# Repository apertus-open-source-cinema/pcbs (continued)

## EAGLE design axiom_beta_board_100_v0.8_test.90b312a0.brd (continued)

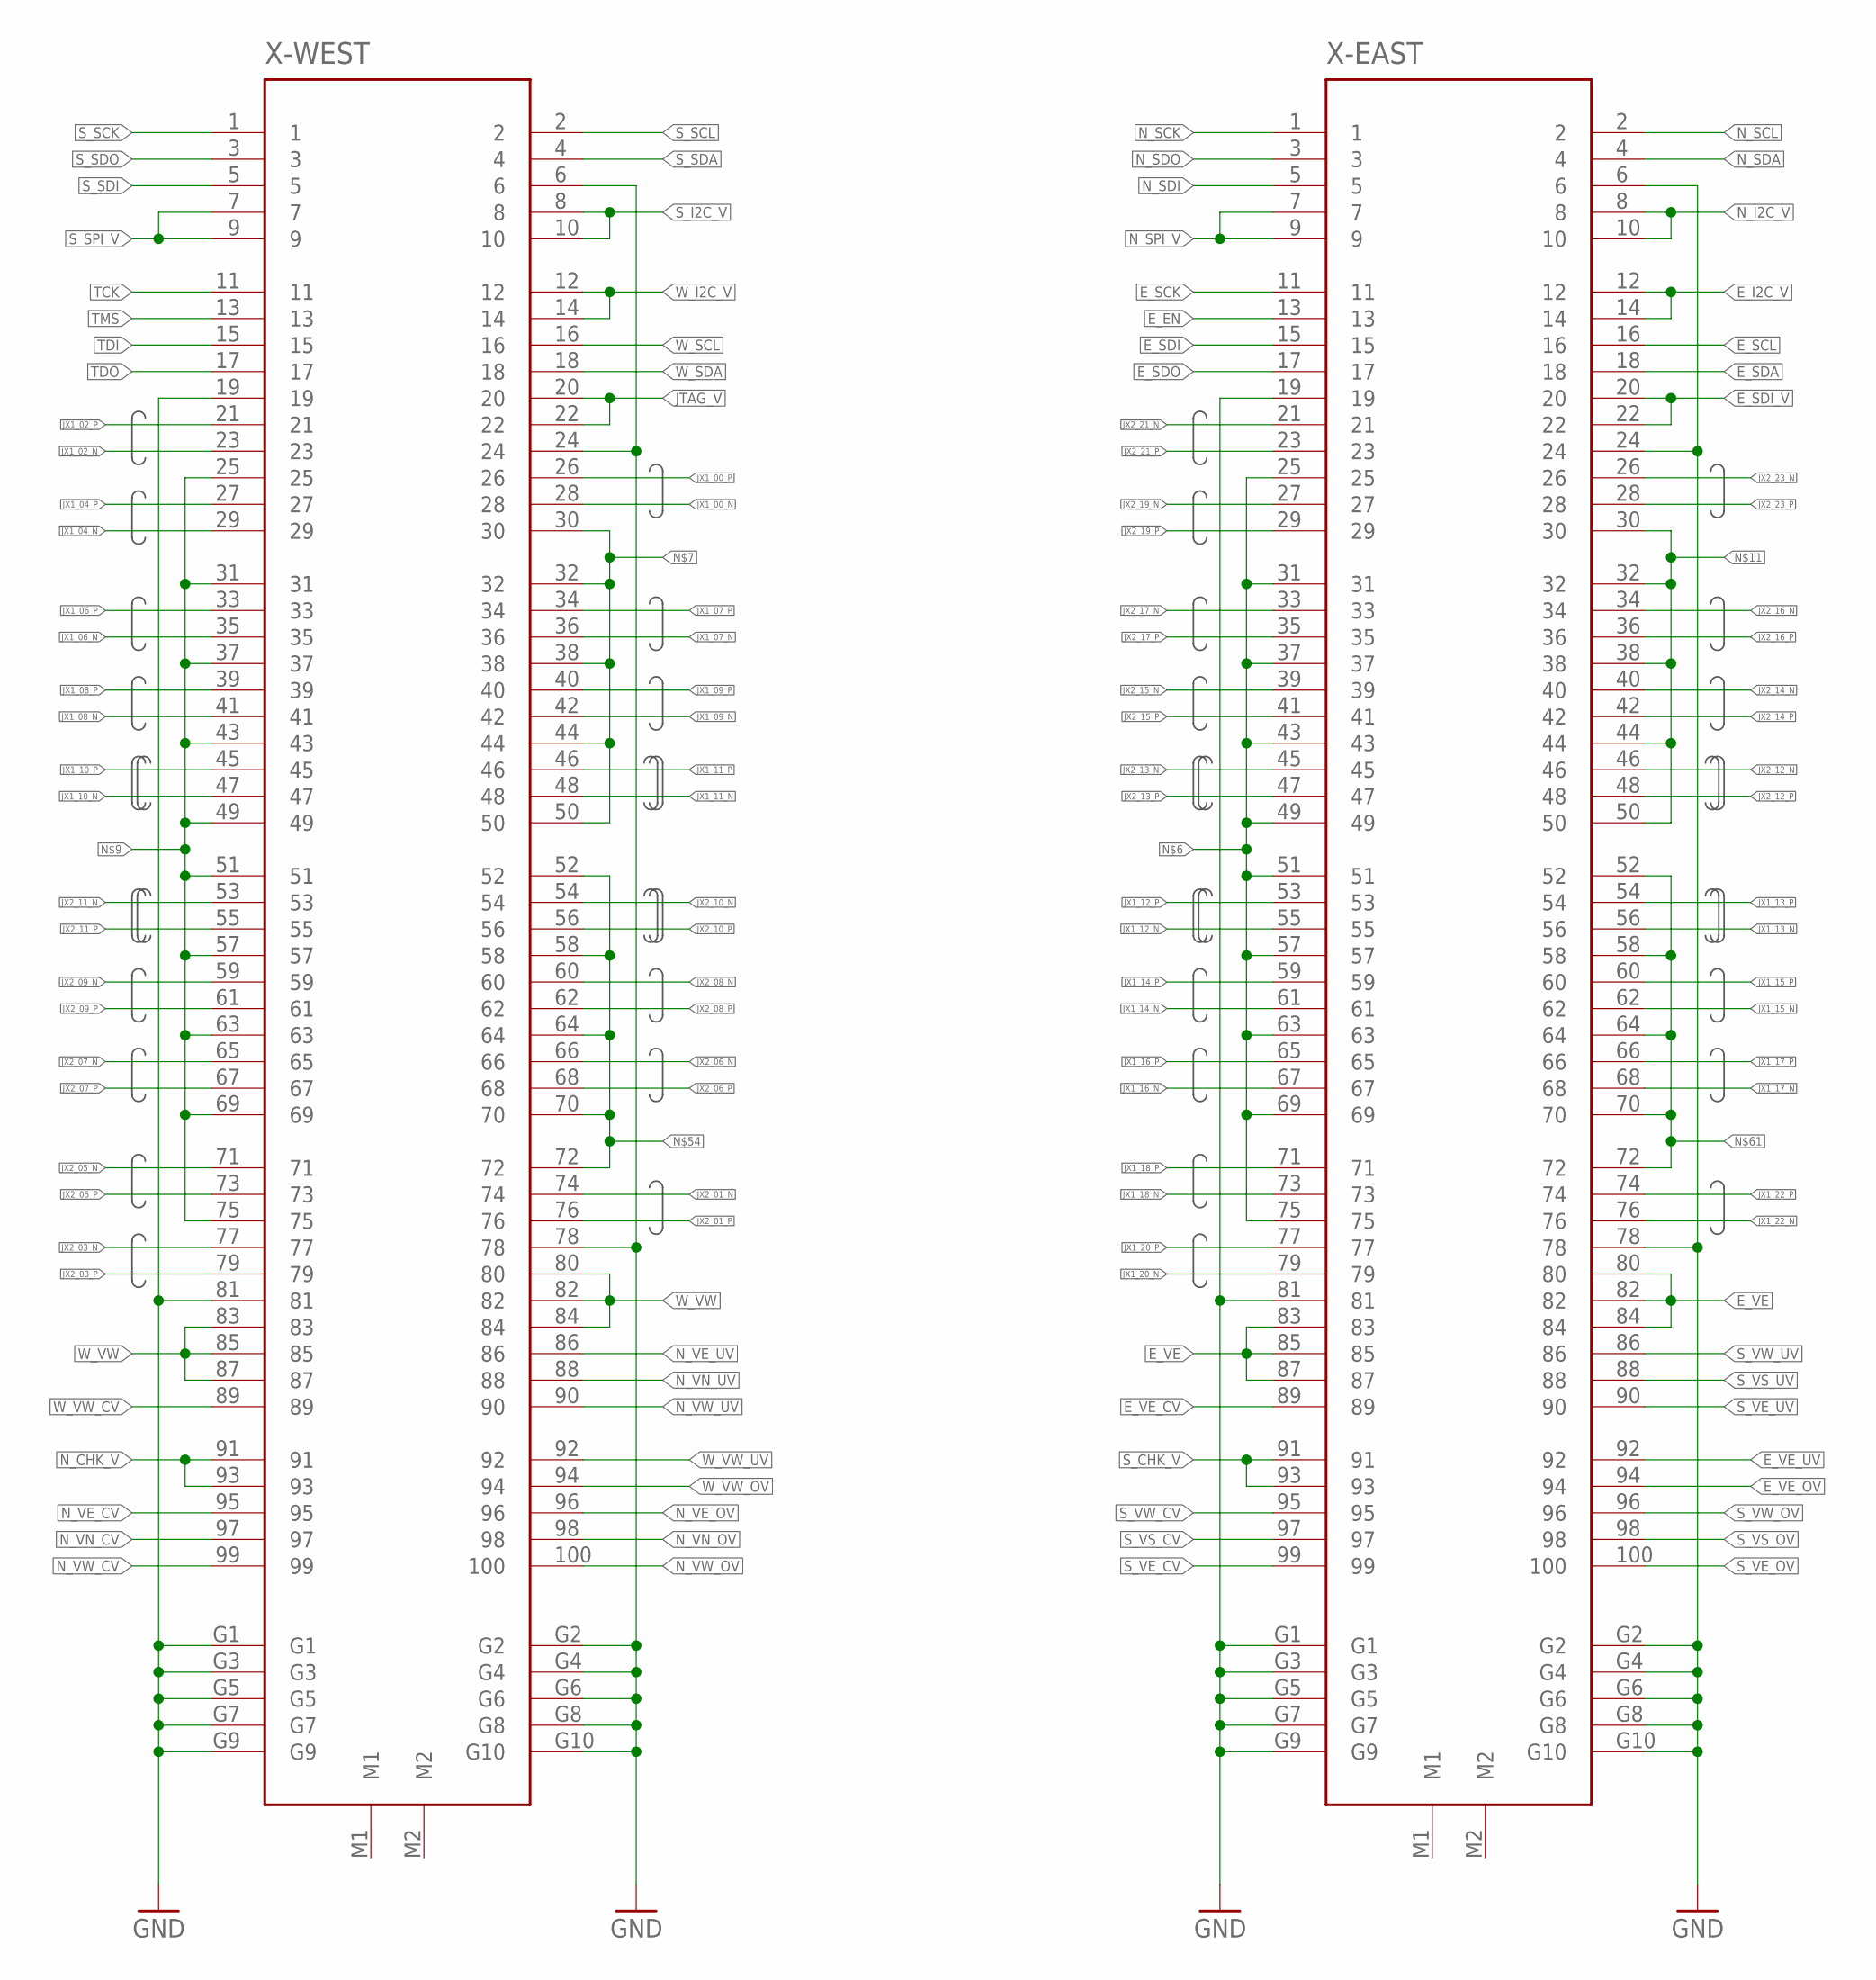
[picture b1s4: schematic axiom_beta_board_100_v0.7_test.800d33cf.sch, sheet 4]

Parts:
X-EAST: FX10-100/10S; FX10A-100S/10
X-WEST: FX10-100/10S; FX10A-100S/10

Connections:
E_EN: X-EAST.13; also elsewhere on the board
E_I2C_V: X-EAST.12, X-EAST.14; also elsewhere on the board
E_SCK: X-EAST.11; also elsewhere on the board
E_SCL: X-EAST.16; also elsewhere on the board
E_SDA: X-EAST.18; also elsewhere on the board
E_SDI: X-EAST.15; also elsewhere on the board
E_SDI_V: X-EAST.20, X-EAST.22; also elsewhere on the board
E_SDO: X-EAST.17; also elsewhere on the board
E_VE: X-EAST.80, X-EAST.82, X-EAST.83, X-EAST.84, X-EAST.85, X-EAST.87; also elsewhere on the board
E_VE_CV: X-EAST.89; also elsewhere on the board
E_VE_OV: X-EAST.94; also elsewhere on the board
E_VE_UV: X-EAST.92; also elsewhere on the board
JTAG_V: X-WEST.20, X-WEST.22; also elsewhere on the board
JX1_00_N: X-WEST.28; also elsewhere on the board
JX1_00_P: X-WEST.26; also elsewhere on the board
JX1_02_N: X-WEST.23; also elsewhere on the board
JX1_02_P: X-WEST.21; also elsewhere on the board
JX1_04_N: X-WEST.29; also elsewhere on the board
JX1_04_P: X-WEST.27; also elsewhere on the board
JX1_06_N: X-WEST.35; also elsewhere on the board
JX1_06_P: X-WEST.33; also elsewhere on the board
JX1_07_N: X-WEST.36; also elsewhere on the board
JX1_07_P: X-WEST.34; also elsewhere on the board
JX1_08_N: X-WEST.41; also elsewhere on the board
JX1_08_P: X-WEST.39; also elsewhere on the board
JX1_09_N: X-WEST.42; also elsewhere on the board
JX1_09_P: X-WEST.40; also elsewhere on the board
JX1_10_N: X-WEST.47; also elsewhere on the board
JX1_10_P: X-WEST.45; also elsewhere on the board
JX1_11_N: X-WEST.48; also elsewhere on the board
JX1_11_P: X-WEST.46; also elsewhere on the board
JX1_12_N: X-EAST.55; also elsewhere on the board
JX1_12_P: X-EAST.53; also elsewhere on the board
JX1_13_N: X-EAST.56; also elsewhere on the board
JX1_13_P: X-EAST.54; also elsewhere on the board
JX1_14_N: X-EAST.61; also elsewhere on the board
JX1_14_P: X-EAST.59; also elsewhere on the board
JX1_15_N: X-EAST.62; also elsewhere on the board
JX1_15_P: X-EAST.60; also elsewhere on the board
JX1_16_N: X-EAST.67; also elsewhere on the board
JX1_16_P: X-EAST.65; also elsewhere on the board
JX1_17_N: X-EAST.68; also elsewhere on the board
JX1_17_P: X-EAST.66; also elsewhere on the board
JX1_18_N: X-EAST.73; also elsewhere on the board
JX1_18_P: X-EAST.71; also elsewhere on the board
JX1_20_N: X-EAST.79; also elsewhere on the board
JX1_20_P: X-EAST.77; also elsewhere on the board
JX1_22_N: X-EAST.76; also elsewhere on the board
JX1_22_P: X-EAST.74; also elsewhere on the board
JX2_01_N: X-WEST.74; also elsewhere on the board
JX2_01_P: X-WEST.76; also elsewhere on the board
JX2_03_N: X-WEST.77; also elsewhere on the board
JX2_03_P: X-WEST.79; also elsewhere on the board
JX2_05_N: X-WEST.71; also elsewhere on the board
JX2_05_P: X-WEST.73; also elsewhere on the board
JX2_06_N: X-WEST.66; also elsewhere on the board
JX2_06_P: X-WEST.68; also elsewhere on the board
JX2_07_N: X-WEST.65; also elsewhere on the board
JX2_07_P: X-WEST.67; also elsewhere on the board
JX2_08_N: X-WEST.60; also elsewhere on the board
JX2_08_P: X-WEST.62; also elsewhere on the board
JX2_09_N: X-WEST.59; also elsewhere on the board
JX2_09_P: X-WEST.61; also elsewhere on the board
JX2_10_N: X-WEST.54; also elsewhere on the board
JX2_10_P: X-WEST.56; also elsewhere on the board
JX2_11_N: X-WEST.53; also elsewhere on the board
JX2_11_P: X-WEST.55; also elsewhere on the board
JX2_12_N: X-EAST.46; also elsewhere on the board
JX2_12_P: X-EAST.48; also elsewhere on the board
JX2_13_N: X-EAST.45; also elsewhere on the board
JX2_13_P: X-EAST.47; also elsewhere on the board
JX2_14_N: X-EAST.40; also elsewhere on the board
JX2_14_P: X-EAST.42; also elsewhere on the board
JX2_15_N: X-EAST.39; also elsewhere on the board
JX2_15_P: X-EAST.41; also elsewhere on the board
JX2_16_N: X-EAST.34; also elsewhere on the board
JX2_16_P: X-EAST.36; also elsewhere on the board
JX2_17_N: X-EAST.33; also elsewhere on the board
JX2_17_P: X-EAST.35; also elsewhere on the board
JX2_19_N: X-EAST.27; also elsewhere on the board
JX2_19_P: X-EAST.29; also elsewhere on the board
JX2_21_N: X-EAST.21; also elsewhere on the board
JX2_21_P: X-EAST.23; also elsewhere on the board
JX2_23_N: X-EAST.26; also elsewhere on the board
JX2_23_P: X-EAST.28; also elsewhere on the board
N_CHK_V: X-WEST.91, X-WEST.93; also elsewhere on the board
N_I2C_V: X-EAST.8, X-EAST.10; also elsewhere on the board
N_SCK: X-EAST.1; also elsewhere on the board
N_SCL: X-EAST.2; also elsewhere on the board
N_SDA: X-EAST.4; also elsewhere on the board
N_SDI: X-EAST.5; also elsewhere on the board
N_SDO: X-EAST.3; also elsewhere on the board
N_SPI_V: X-EAST.7, X-EAST.9; also elsewhere on the board
N_VE_CV: X-WEST.95; also elsewhere on the board
N_VE_OV: X-WEST.96; also elsewhere on the board
N_VE_UV: X-WEST.86; also elsewhere on the board
N_VN_CV: X-WEST.97; also elsewhere on the board
N_VN_OV: X-WEST.98; also elsewhere on the board
N_VN_UV: X-WEST.88; also elsewhere on the board
N_VW_CV: X-WEST.99; also elsewhere on the board
N_VW_OV: X-WEST.100; also elsewhere on the board
N_VW_UV: X-WEST.90; also elsewhere on the board
S_CHK_V: X-EAST.91, X-EAST.93; also elsewhere on the board
S_I2C_V: X-WEST.8, X-WEST.10; also elsewhere on the board
S_SCK: X-WEST.1; also elsewhere on the board
S_SCL: X-WEST.2; also elsewhere on the board
S_SDA: X-WEST.4; also elsewhere on the board
S_SDI: X-WEST.5; also elsewhere on the board
S_SDO: X-WEST.3; also elsewhere on the board
S_SPI_V: X-WEST.7, X-WEST.9; also elsewhere on the board
S_VE_CV: X-EAST.99; also elsewhere on the board
S_VE_OV: X-EAST.100; also elsewhere on the board
S_VE_UV: X-EAST.90; also elsewhere on the board
S_VS_CV: X-EAST.97; also elsewhere on the board
S_VS_OV: X-EAST.98; also elsewhere on the board
S_VS_UV: X-EAST.88; also elsewhere on the board
S_VW_CV: X-EAST.95; also elsewhere on the board
S_VW_OV: X-EAST.96; also elsewhere on the board
S_VW_UV: X-EAST.86; also elsewhere on the board
TCK: X-WEST.11; also elsewhere on the board
TDI: X-WEST.15; also elsewhere on the board
TDO: X-WEST.17; also elsewhere on the board
TMS: X-WEST.13; also elsewhere on the board
W_I2C_V: X-WEST.12, X-WEST.14; also elsewhere on the board
W_SCL: X-WEST.16; also elsewhere on the board
W_SDA: X-WEST.18; also elsewhere on the board
W_VW: X-WEST.80, X-WEST.82, X-WEST.83, X-WEST.84, X-WEST.85, X-WEST.87; also elsewhere on the board
W_VW_CV: X-WEST.89; also elsewhere on the board
W_VW_OV: X-WEST.94; also elsewhere on the board
W_VW_UV: X-WEST.92; also elsewhere on the board

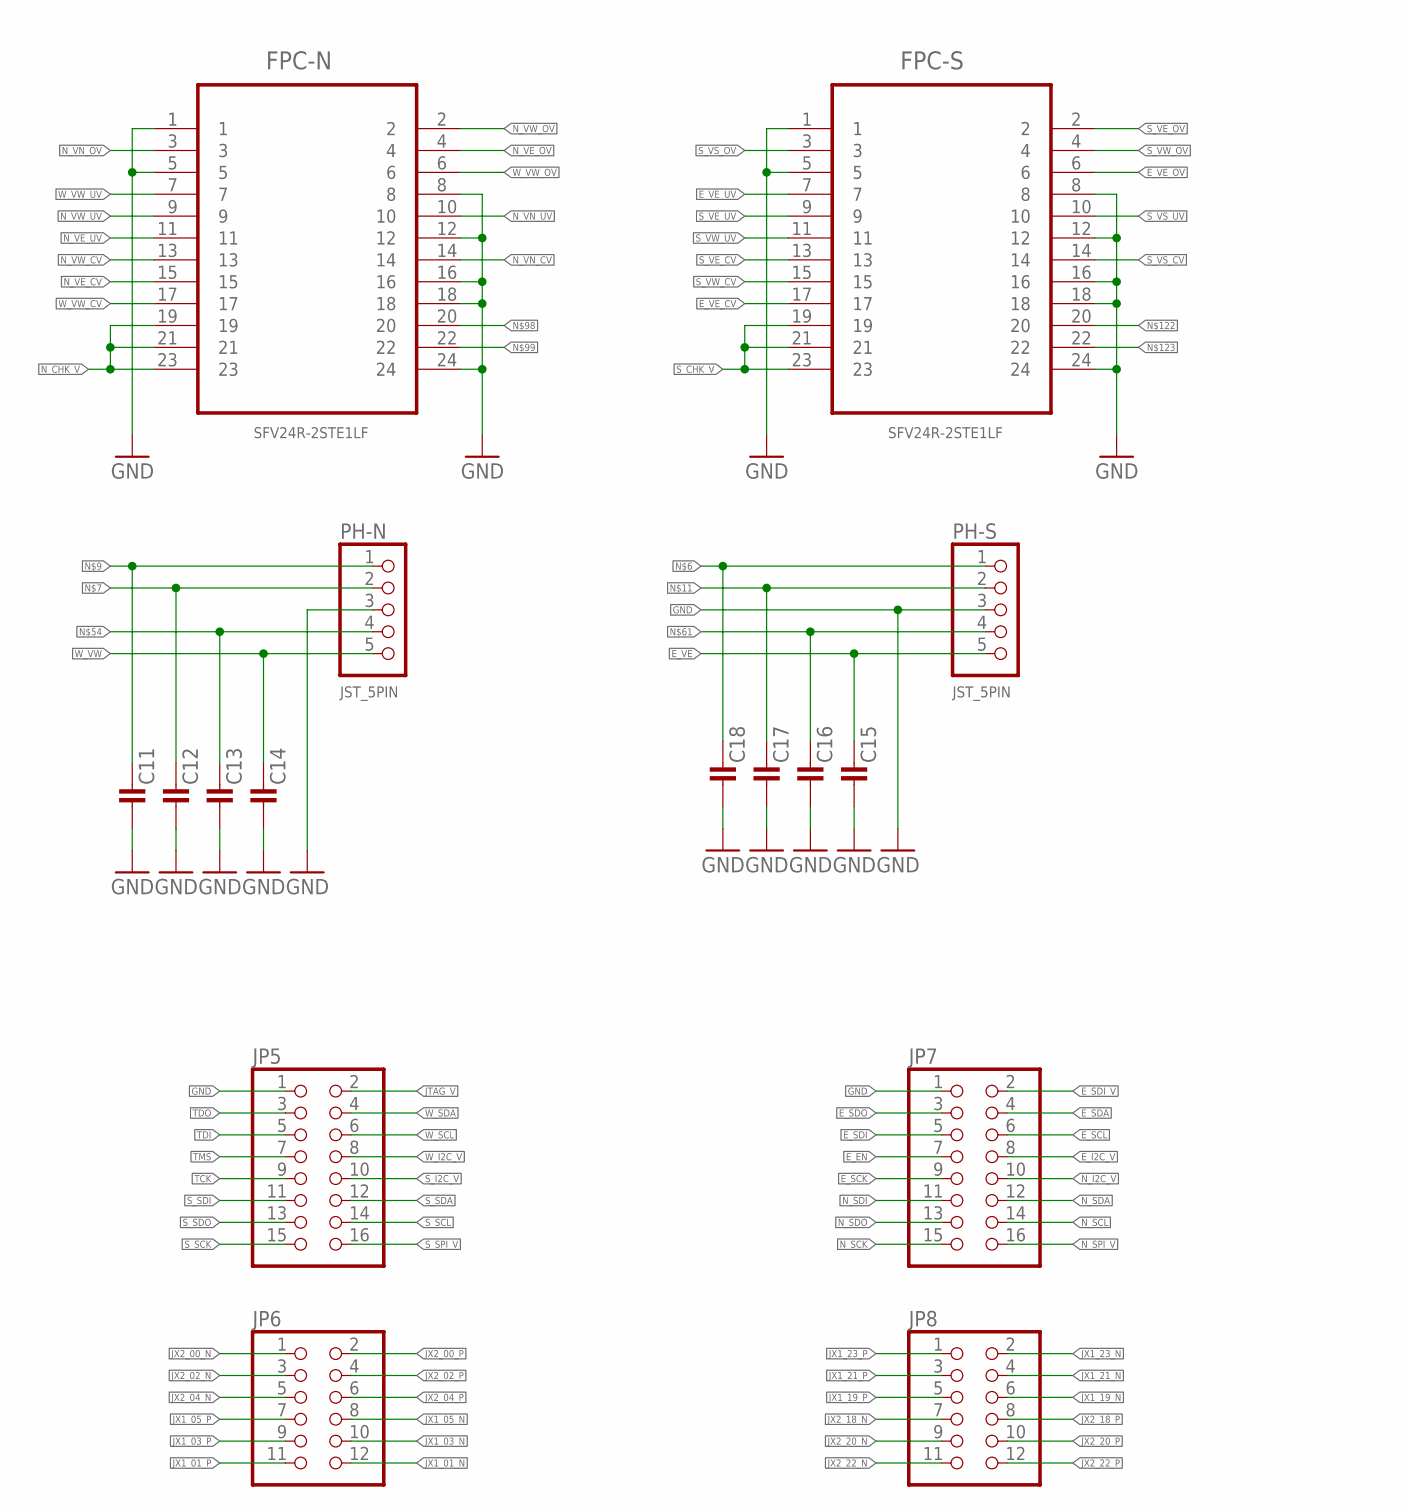
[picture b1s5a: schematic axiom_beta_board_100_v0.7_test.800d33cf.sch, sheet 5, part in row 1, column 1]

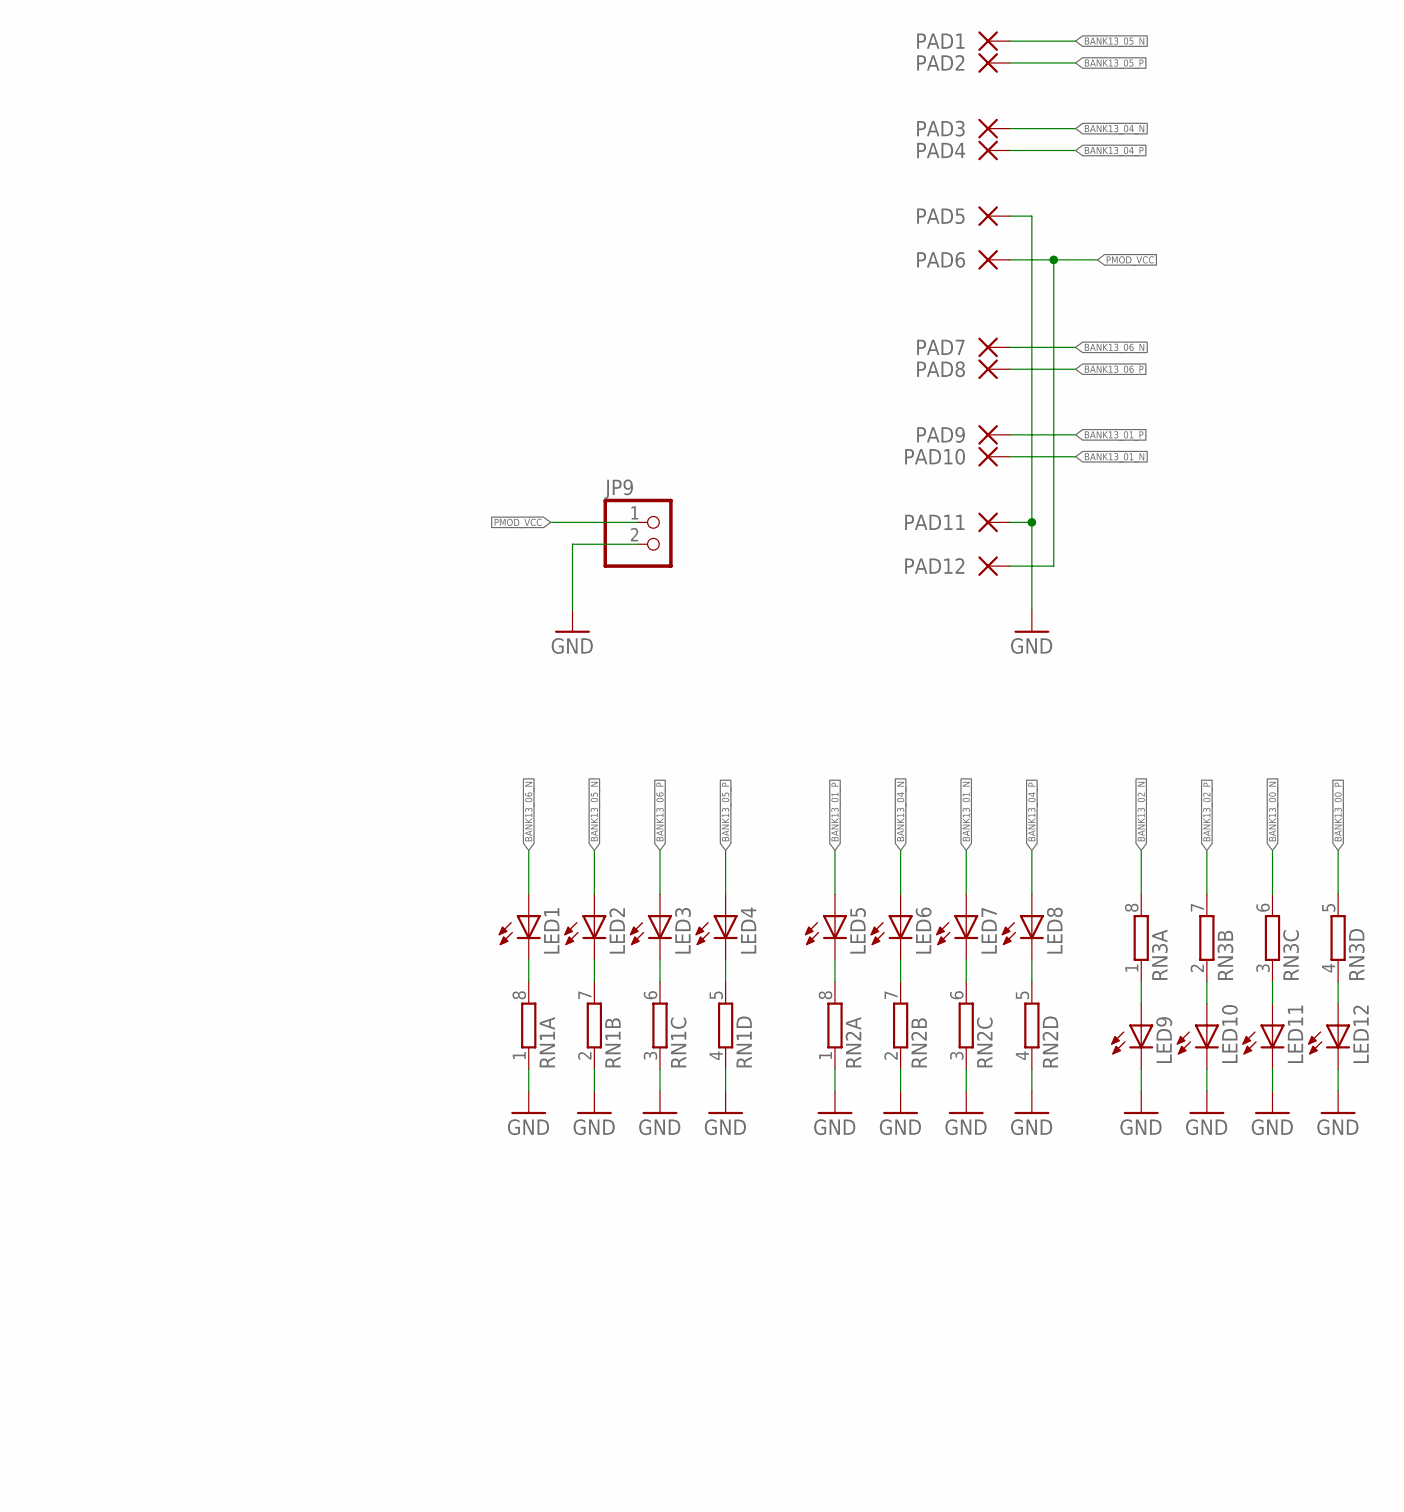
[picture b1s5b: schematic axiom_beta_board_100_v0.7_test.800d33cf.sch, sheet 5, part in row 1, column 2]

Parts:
C11, C12, C13, C14, C15, C16, C17, C18: C1206-B; 1206-B
FPC-N: SFV24R-2STE1LF; FCI_SFV24R-2STE1LF
FPC-S: SFV24R-2STE1LF; FCI_SFV24R-2STE1LF
JP5, JP7: PINHD-2X08_2.54; 2X08
JP6, JP8: PINHD-2X06_2.54; 2X06
JP9: PINHD-1X02_2.54; 1X02
LED1, LED2, LED3, LED4, LED5, LED6, LED7, LED8, LED9, LED10, LED11, LED12: LEDCHIPLED_0603; CHIPLED_0603
PAD1, PAD2, PAD3, PAD4, PAD5, PAD6, PAD7, PAD8, PAD9, PAD10, PAD11, PAD12: SMD-PAD1.6X3.8MM-U; 1.6X3.8U-MM
PH-N: JST_5PIN; JST-PH-5-SMT-RA
PH-S: JST_5PIN; JST-PH-5-SMT-RA
RN1, RN2, RN3: 4R-NCAY16; CAY16

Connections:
BANK13_00_N: RN3.6 (2); also elsewhere on the board
BANK13_00_P: RN3.5 (2); also elsewhere on the board
BANK13_01_N: LED7.A, PAD10.1; also elsewhere on the board
BANK13_01_P: LED5.A, PAD9.1; also elsewhere on the board
BANK13_02_N: RN3.8 (2); also elsewhere on the board
BANK13_02_P: RN3.7 (2); also elsewhere on the board
BANK13_04_N: LED6.A, PAD3.1; also elsewhere on the board
BANK13_04_P: LED8.A, PAD4.1; also elsewhere on the board
BANK13_05_N: LED2.A, PAD1.1; also elsewhere on the board
BANK13_05_P: LED4.A, PAD2.1; also elsewhere on the board
BANK13_06_N: LED1.A, PAD7.1; also elsewhere on the board
BANK13_06_P: LED3.A, PAD8.1; also elsewhere on the board
E_EN: JP7.7; also elsewhere on the board
E_I2C_V: JP7.8; also elsewhere on the board
E_SCK: JP7.9; also elsewhere on the board
E_SCL: JP7.6; also elsewhere on the board
E_SDA: JP7.4; also elsewhere on the board
E_SDI: JP7.5; also elsewhere on the board
E_SDI_V: JP7.2; also elsewhere on the board
E_SDO: JP7.3; also elsewhere on the board
E_VE: C15.1, PH-S.5; also elsewhere on the board
E_VE_CV: FPC-S.17; also elsewhere on the board
E_VE_OV: FPC-S.6; also elsewhere on the board
E_VE_UV: FPC-S.7; also elsewhere on the board
JTAG_V: JP5.2; also elsewhere on the board
JX1_01_N: JP6.12; also elsewhere on the board
JX1_01_P: JP6.11; also elsewhere on the board
JX1_03_N: JP6.10; also elsewhere on the board
JX1_03_P: JP6.9; also elsewhere on the board
JX1_05_N: JP6.8; also elsewhere on the board
JX1_05_P: JP6.7; also elsewhere on the board
JX1_19_N: JP8.6; also elsewhere on the board
JX1_19_P: JP8.5; also elsewhere on the board
JX1_21_N: JP8.4; also elsewhere on the board
JX1_21_P: JP8.3; also elsewhere on the board
JX1_23_N: JP8.2; also elsewhere on the board
JX1_23_P: JP8.1; also elsewhere on the board
JX2_00_N: JP6.1; also elsewhere on the board
JX2_00_P: JP6.2; also elsewhere on the board
JX2_02_N: JP6.3; also elsewhere on the board
JX2_02_P: JP6.4; also elsewhere on the board
JX2_04_N: JP6.5; also elsewhere on the board
JX2_04_P: JP6.6; also elsewhere on the board
JX2_18_N: JP8.7; also elsewhere on the board
JX2_18_P: JP8.8; also elsewhere on the board
JX2_20_N: JP8.9; also elsewhere on the board
JX2_20_P: JP8.10; also elsewhere on the board
JX2_22_N: JP8.11; also elsewhere on the board
JX2_22_P: JP8.12; also elsewhere on the board
unnamed: LED1.C, RN1.8 (2)
unnamed: LED2.C, RN1.7 (2)
unnamed: LED3.C, RN1.6 (2)
unnamed: LED4.C, RN1.5 (2)
unnamed: LED5.C, RN2.8 (2)
unnamed: LED6.C, RN2.7 (2)
unnamed: LED7.C, RN2.6 (2)
unnamed: LED8.C, RN2.5 (2)
unnamed: LED9.A, RN3.1
unnamed: LED10.A, RN3.2 (1)
unnamed: LED11.A, RN3.3 (1)
unnamed: LED12.A, RN3.4 (1)
N_CHK_V: FPC-N.19, FPC-N.21, FPC-N.23; also elsewhere on the board
N_I2C_V: JP7.10; also elsewhere on the board
N_SCK: JP7.15; also elsewhere on the board
N_SCL: JP7.14; also elsewhere on the board
N_SDA: JP7.12; also elsewhere on the board
N_SDI: JP7.11; also elsewhere on the board
N_SDO: JP7.13; also elsewhere on the board
N_SPI_V: JP7.16; also elsewhere on the board
N_VE_CV: FPC-N.15; also elsewhere on the board
N_VE_OV: FPC-N.4; also elsewhere on the board
N_VE_UV: FPC-N.11; also elsewhere on the board
N_VN_CV: FPC-N.14; also elsewhere on the board
N_VN_OV: FPC-N.3; also elsewhere on the board
N_VN_UV: FPC-N.10; also elsewhere on the board
N_VW_CV: FPC-N.13; also elsewhere on the board
N_VW_OV: FPC-N.2; also elsewhere on the board
N_VW_UV: FPC-N.9; also elsewhere on the board
PMOD_VCC: JP9.1, PAD6.1, PAD12.1
S_CHK_V: FPC-S.19, FPC-S.21, FPC-S.23; also elsewhere on the board
S_I2C_V: JP5.10; also elsewhere on the board
S_SCK: JP5.15; also elsewhere on the board
S_SCL: JP5.14; also elsewhere on the board
S_SDA: JP5.12; also elsewhere on the board
S_SDI: JP5.11; also elsewhere on the board
S_SDO: JP5.13; also elsewhere on the board
S_SPI_V: JP5.16; also elsewhere on the board
S_VE_CV: FPC-S.13; also elsewhere on the board
S_VE_OV: FPC-S.2; also elsewhere on the board
S_VE_UV: FPC-S.9; also elsewhere on the board
S_VS_CV: FPC-S.14; also elsewhere on the board
S_VS_OV: FPC-S.3; also elsewhere on the board
S_VS_UV: FPC-S.10; also elsewhere on the board
S_VW_CV: FPC-S.15; also elsewhere on the board
S_VW_OV: FPC-S.4; also elsewhere on the board
S_VW_UV: FPC-S.11; also elsewhere on the board
TCK: JP5.9; also elsewhere on the board
TDI: JP5.5; also elsewhere on the board
TDO: JP5.3; also elsewhere on the board
TMS: JP5.7; also elsewhere on the board
W_I2C_V: JP5.8; also elsewhere on the board
W_SCL: JP5.6; also elsewhere on the board
W_SDA: JP5.4; also elsewhere on the board
W_VW: C14.1, PH-N.5; also elsewhere on the board
W_VW_CV: FPC-N.17; also elsewhere on the board
W_VW_OV: FPC-N.6; also elsewhere on the board
W_VW_UV: FPC-N.7; also elsewhere on the board

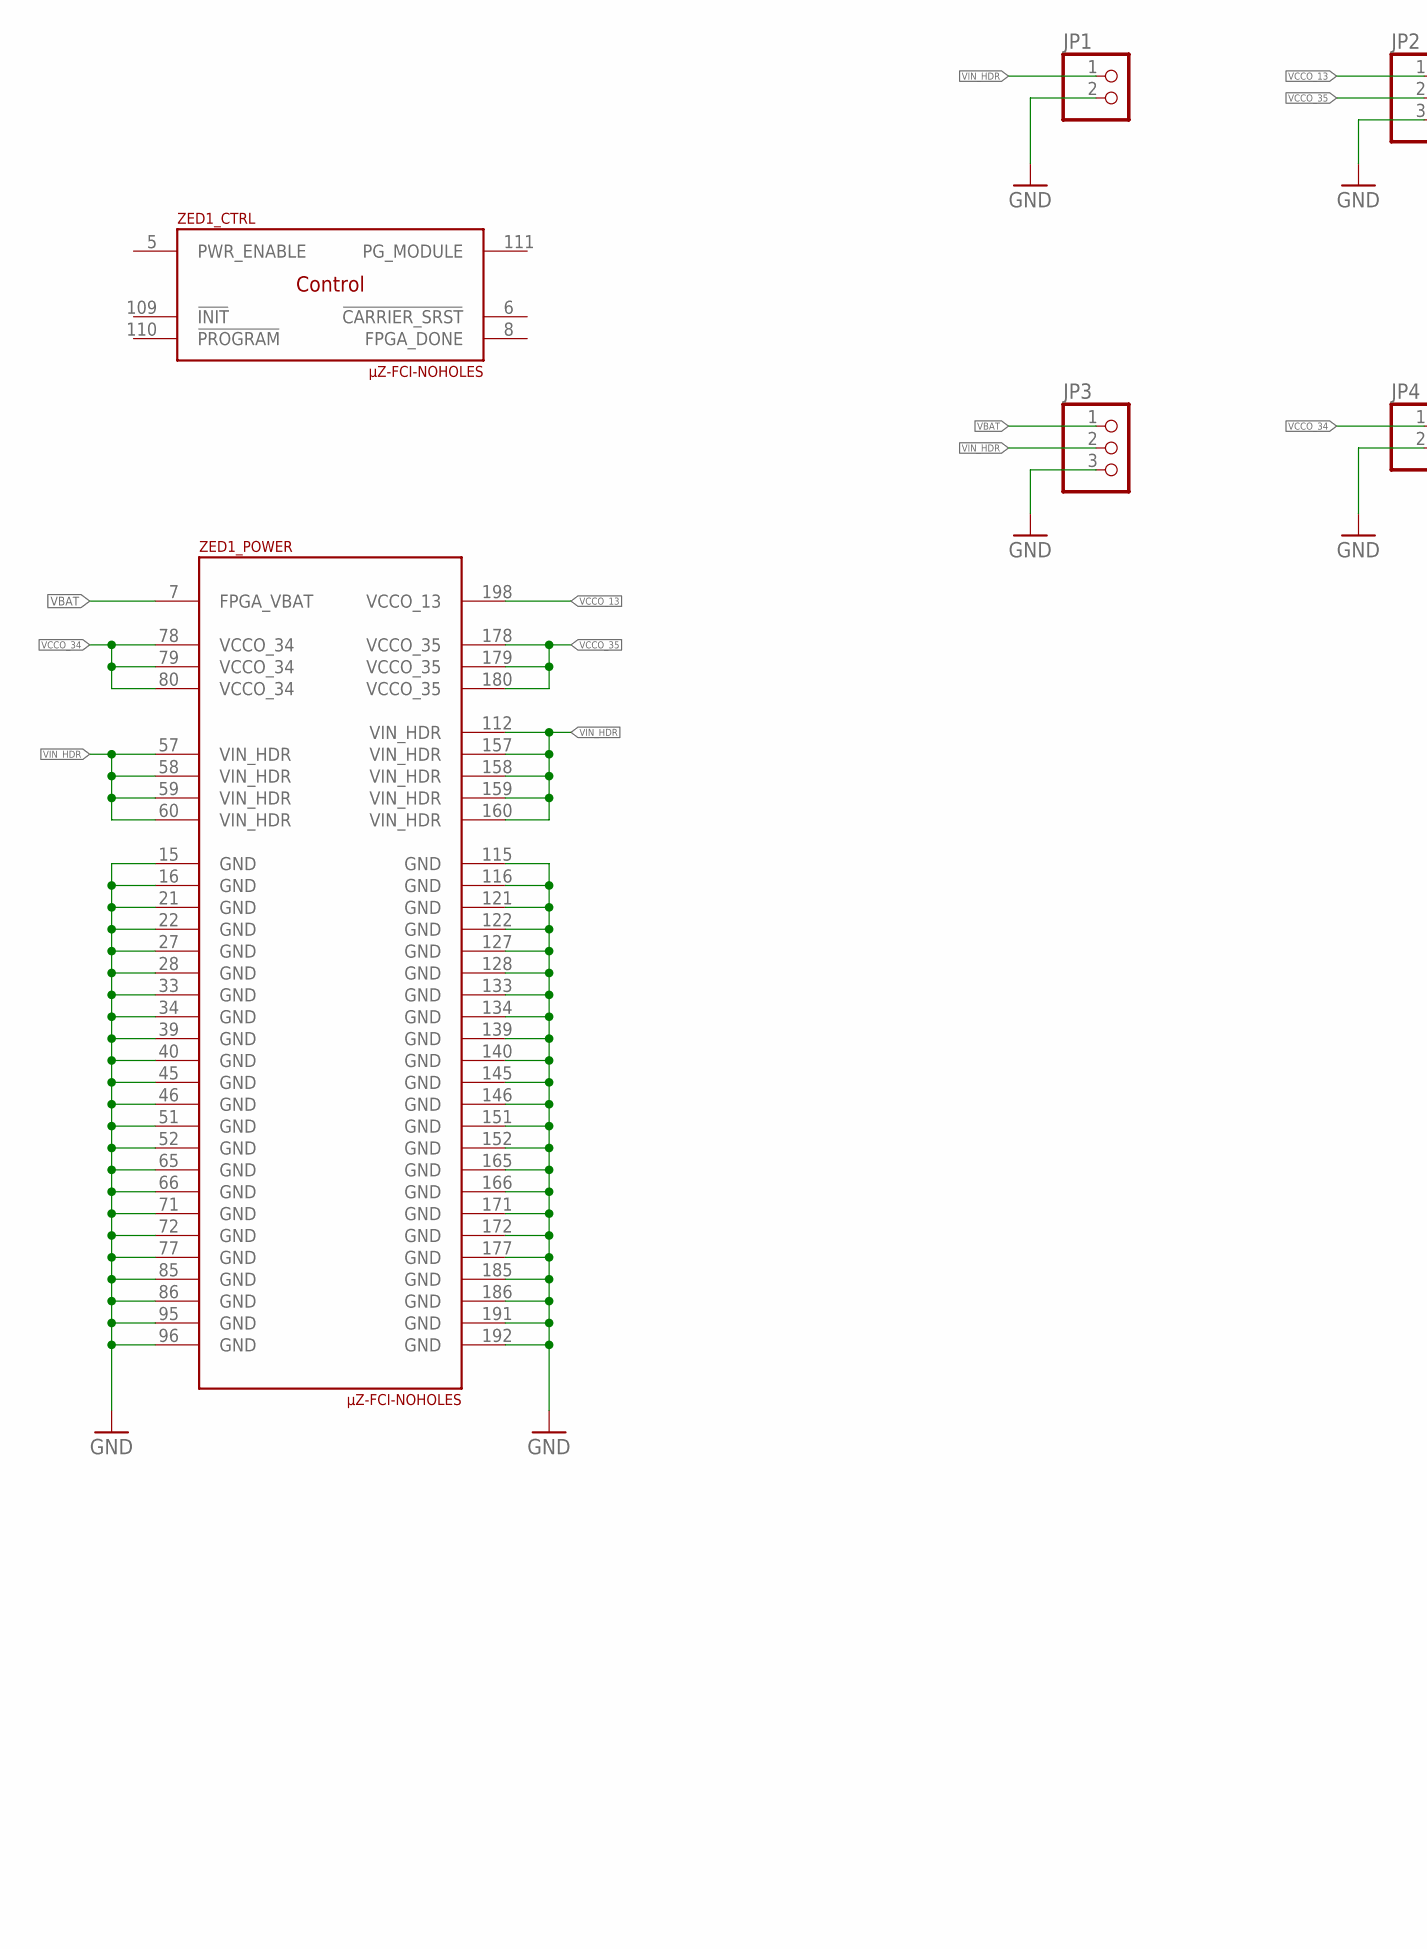
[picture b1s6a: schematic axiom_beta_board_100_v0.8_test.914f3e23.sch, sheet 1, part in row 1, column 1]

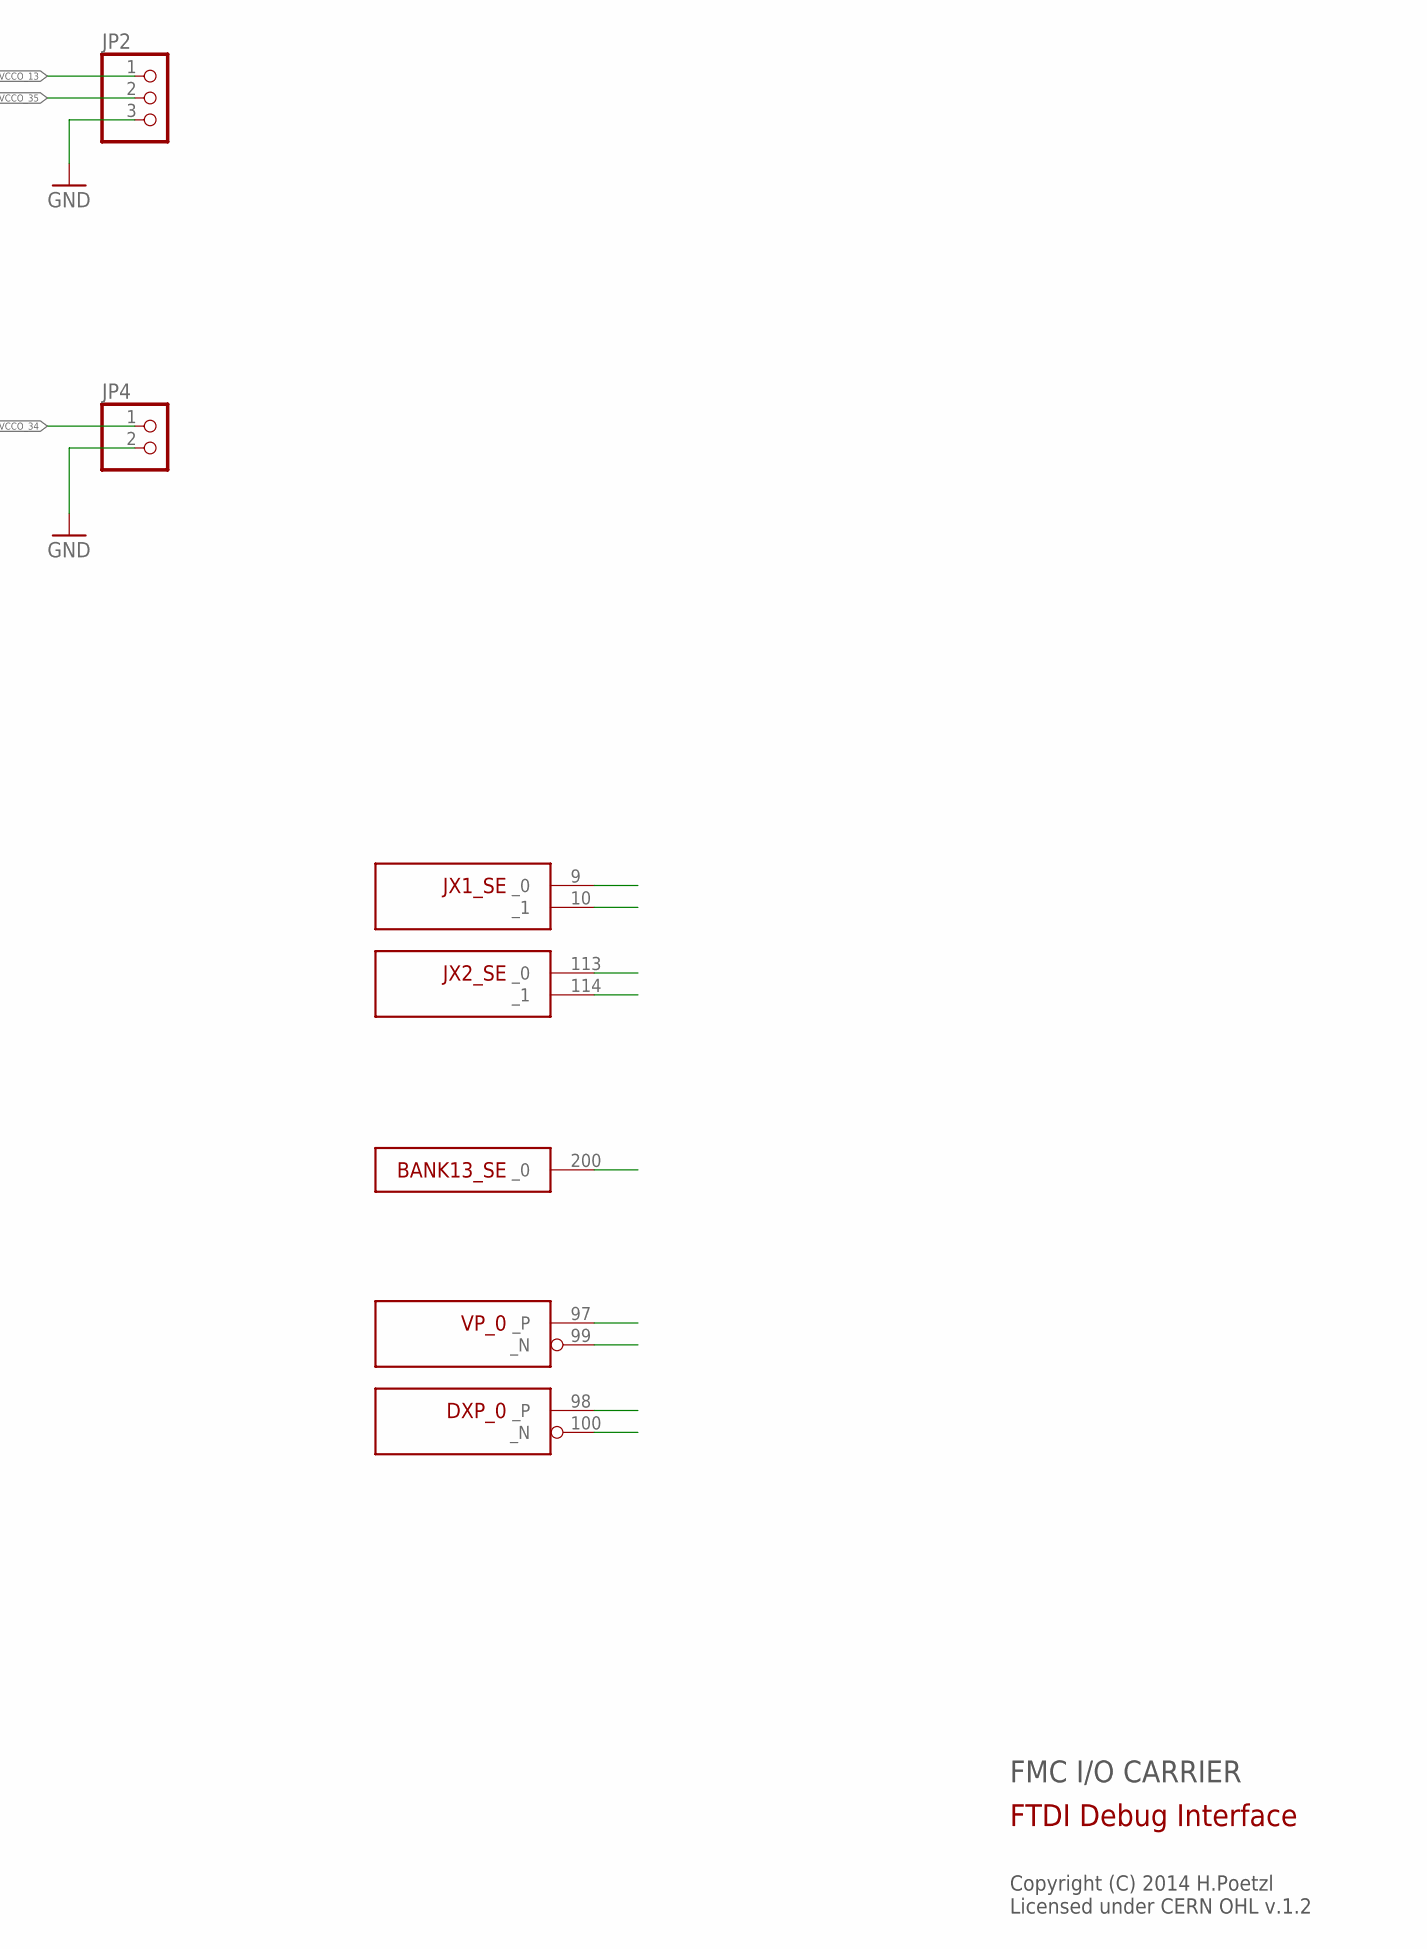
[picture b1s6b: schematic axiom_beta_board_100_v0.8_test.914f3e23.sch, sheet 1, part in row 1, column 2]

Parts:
JP1, JP4: PINHD-1X02_2.54; 1X02
JP2, JP3: PINHD-1X03_2.54; 1X03
ZED1: µZ-FCI-NOHOLES; µZ-NOHOLES

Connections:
VBAT: JP3.1, ZED1.7 (FPGA_VBAT)
VCCO_13: JP2.1, ZED1.198 (VCCO_13)
VCCO_34: JP4.1, ZED1.78 (VCCO_34), ZED1.79 (VCCO_34), ZED1.80 (VCCO_34)
VCCO_35: JP2.2, ZED1.178 (VCCO_35), ZED1.179 (VCCO_35), ZED1.180 (VCCO_35)
VIN_HDR: JP1.1, JP3.2, ZED1.57 (VIN_HDR), ZED1.58 (VIN_HDR), ZED1.59 (VIN_HDR), ZED1.60 (VIN_HDR), ZED1.112 (VIN_HDR), ZED1.157 (VIN_HDR), ZED1.158 (VIN_HDR), ZED1.159 (VIN_HDR), ZED1.160 (VIN_HDR)

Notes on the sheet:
FMC I/O CARRIER
Copyright (C) 2014 H.Poetzl Licensed under CERN OHL v.1.2
FTDI Debug Interface
